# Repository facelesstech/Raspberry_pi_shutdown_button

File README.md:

# Raspberry_pi_shutdown_button
Simple button and led to shutdown the raspberry pi safely

Blog post - https://facelesstech.wordpress.com/2016/01/16/shut-it-down-raspberry-pi-that-is/

Video - https://youtu.be/Vks5K6tFxGQ

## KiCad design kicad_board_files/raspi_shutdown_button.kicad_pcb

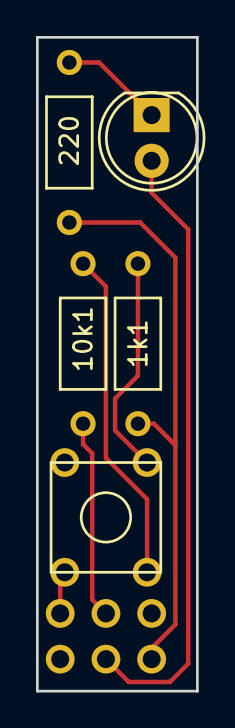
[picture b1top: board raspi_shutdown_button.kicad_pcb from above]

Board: 2 copper layers, 8.9 x 36.3 mm, 6 parts (0 on the bottom side), 6 nets.

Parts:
1k1, 10k1, 220: R; Resistor_Horizontal_RM9mm
D1: LED; LED-5MM
SW1: SW_PUSH; button_long_custom
U1: raspi_button_GPIO

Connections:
unnamed: 1k1.2, U1.3
unnamed: 10k1.1, 220.2, U1.2
unnamed: 1k1.1, 10k1.2, SW1.1
unnamed: 220.1, D1.1
unnamed: D1.2, U1.4
unnamed: SW1.2, U1.1

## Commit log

2015-12-09 rev A untested, Awaiting board from the fab
2015-12-09 python script you will need to work with the button
2016-01-16 added video and blog post links
2016-09-24 Added board files
